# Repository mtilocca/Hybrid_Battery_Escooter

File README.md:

# Hybrid_Battery_Escooter
In this repository it is presented the work related to the B.sc. thesis, where an High Performance Hybrid Battery circuit was developed for an E-scooter.

In this project is presented a strategy aimed at the development of a DC-DC converter best suited to operate in an HESS configuration using HP and HE battery types in a Dual- cell architecture for E-scooter application.
The core feature of the active parallel HESS configuration proposed was represented by the development and testing of a bidirectional DC-DC converter. Which needs to operate either as a boost and either as a buck converter. Through that a 3- phase BLDC was supplied with the energy stored in the UC bank during accelerations of the ES, while it recharged the UC bank during regenerative braking.
It was first simulated the acceleration behavior of an ES. The parameters obtained from that were used for designing the DC- DC converter. According to its requirements a control algorithm was developed in Arduino. Consequently empirical tests were performed to validate the converter and the developed control algorithm.

## System Architecture 

## PCB Schematics 

## Experimental Results

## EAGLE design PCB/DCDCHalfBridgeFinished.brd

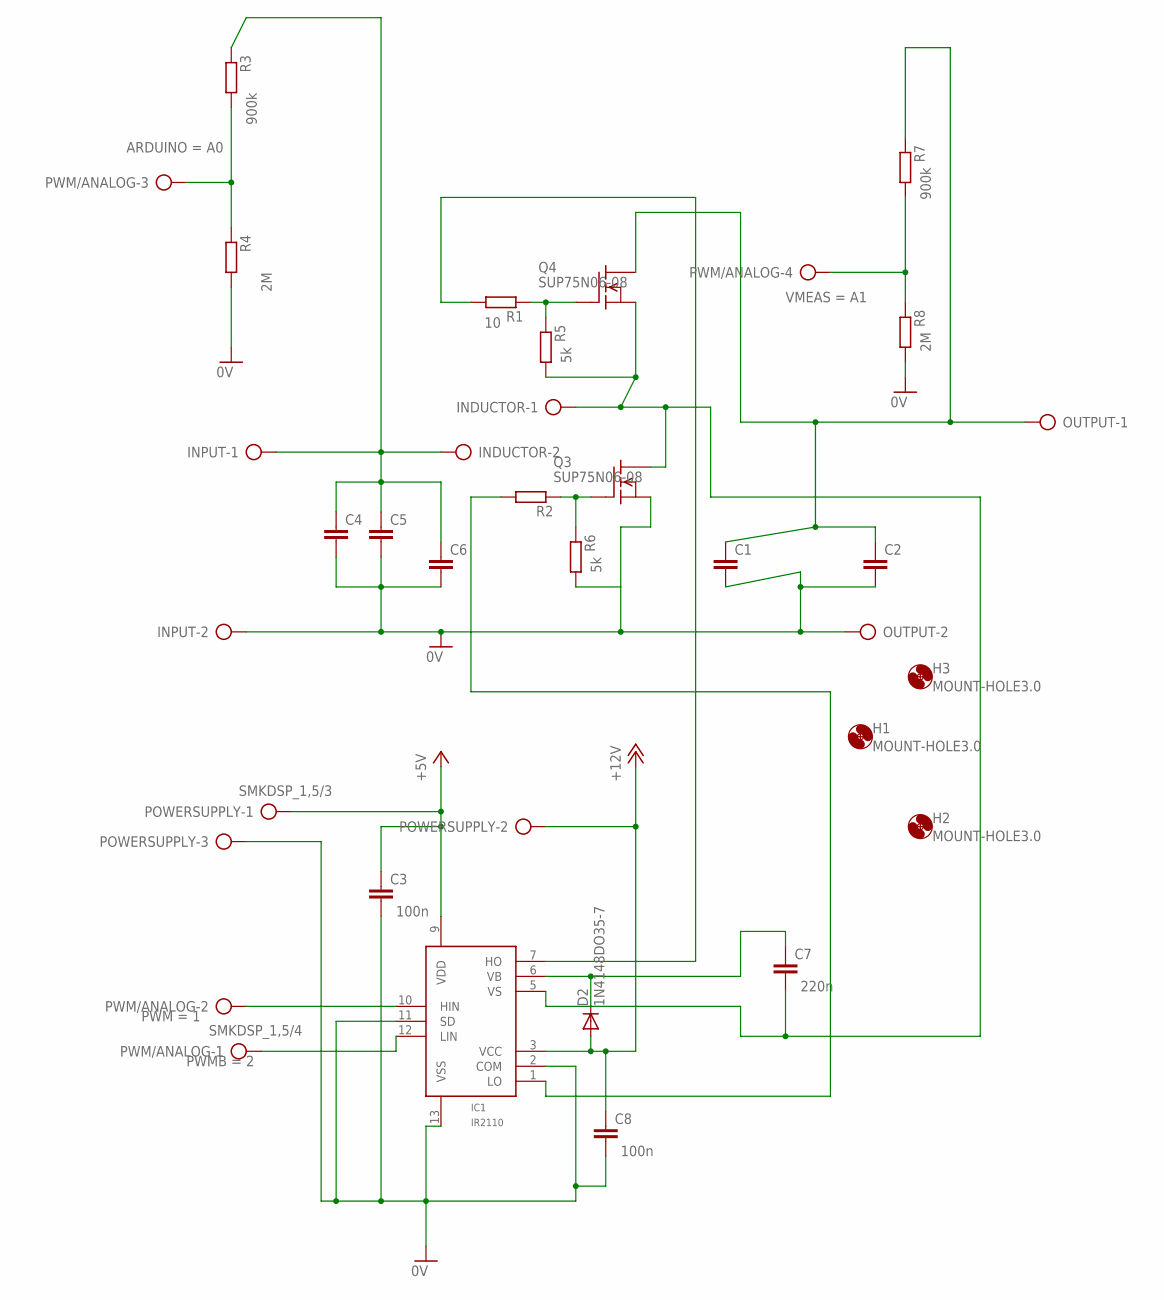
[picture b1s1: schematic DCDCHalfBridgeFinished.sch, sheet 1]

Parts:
C1, C2, C4, C5, C6: C-EU050-025X075; C050-025X075
C3, C7, C8: C-EU025-025X050; C025-025X050
D2: 1N4148DO35-7; DO35-7
H1, H2, H3: MOUNT-HOLE3.0; 3,0
IC1: IR2110; DIL14
INDUCTOR: AK300/2
INPUT: AK300/2
OUTPUT: AK300/2
POWERSUPPLY: SMKDSP_1,5/3
PWM/ANALOG: SMKDSP_1,5/4
Q3, Q4: SUP75N06-08; TO220
R1, R2, R3, R4, R5, R6, R7, R8: R-EU_0204/7; 0204/7

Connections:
+5V: C3.1, IC1.9 (VDD), POWERSUPPLY.1
+12V: C8.1, D2.A, IC1.3 (VCC), POWERSUPPLY.2
GND: C1.2, C2.2, C3.2, C4.2, C5.2, C6.2, C8.2, IC1.2 (COM), IC1.11 (SD), IC1.13 (VSS), INPUT.2, OUTPUT.2, POWERSUPPLY.3, Q3.3 (S), R4.2, R6.2, R8.2
unnamed: PWM/ANALOG.3, R3.2, R4.1
unnamed: IC1.12 (LIN), PWM/ANALOG.1
unnamed: IC1.10 (HIN), PWM/ANALOG.2
unnamed: C7.2, IC1.5 (VS), INDUCTOR.1, Q3.2 (D), Q4.3 (S), R5.2
unnamed: IC1.1 (LO), R2.2
unnamed: Q4.1 (G), R1.1, R5.1
unnamed: Q3.1 (G), R2.1, R6.1
unnamed: PWM/ANALOG.4, R7.2, R8.1
unnamed: C7.1, D2.C, IC1.6 (VB)
unnamed: C1.1, C2.1, OUTPUT.1, Q4.2 (D), R7.1
unnamed: IC1.7 (HO), R1.2
unnamed: C4.1, C5.1, C6.1, INDUCTOR.2, INPUT.1, R3.1

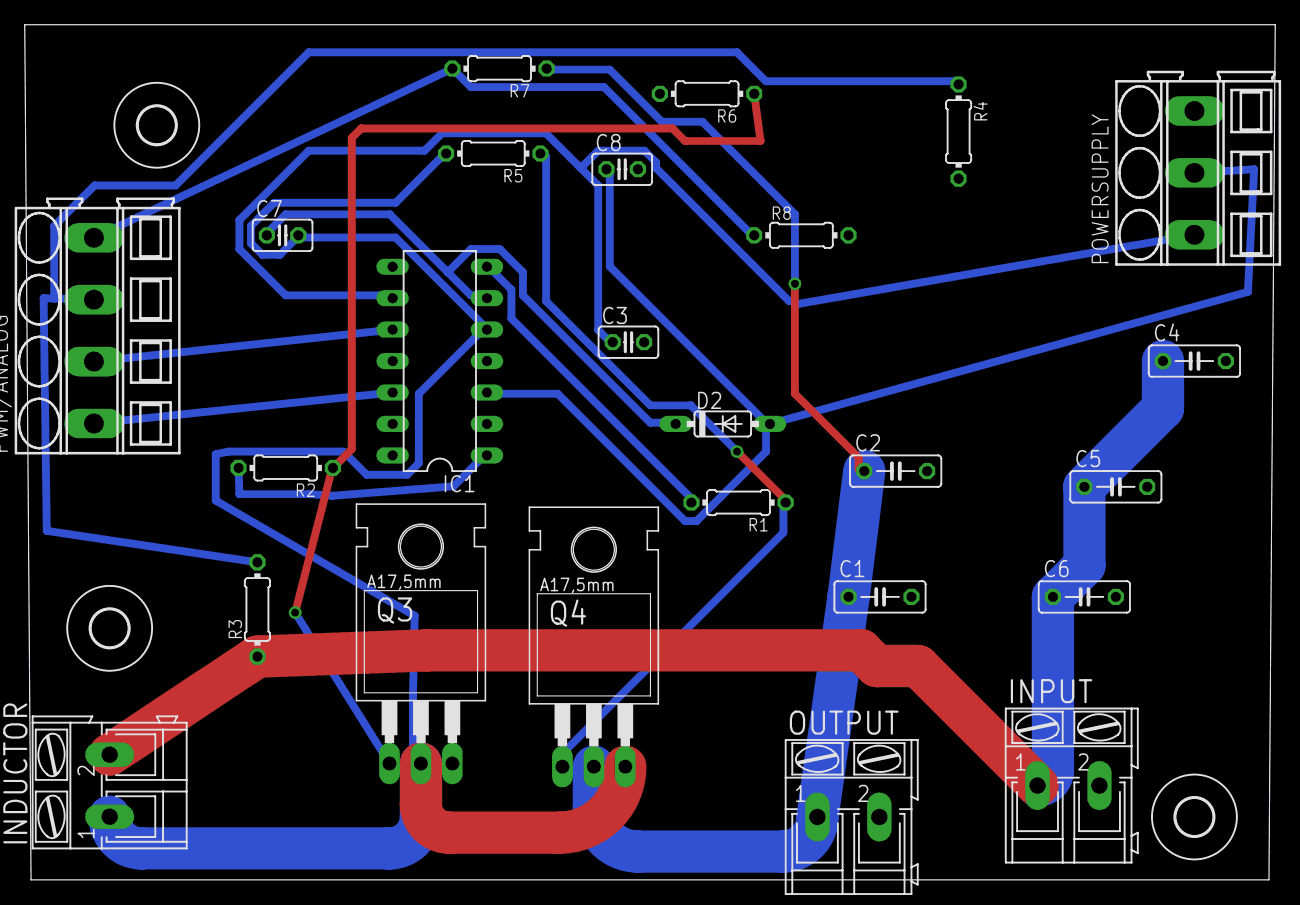
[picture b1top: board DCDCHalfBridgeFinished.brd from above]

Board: 2 copper layers, 101.0 x 69.1 mm, 28 parts (0 on the bottom side), 15 nets.

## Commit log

2022-07-20 Paper
2022-07-20 BEP files upload
